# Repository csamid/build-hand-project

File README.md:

# CSULB BUILD Hand Project

As an CSULB NIH BUILD Scholar I worked in the Robotics and Interactive Systems Engineering laboratory on a hand rehabilitation project. This project was co-advised by Dr. Panadda Marayong and Dr. I-Hung Khoo (many thanks to them!). The goal of our project was to measure hand forces and torques for evaluation and rehabilitative training of individuals with hand impairment. Our project consists of a knob device and a grip-load device to simulate interactions that involve power and precision. Below you can find more details on each device and some other work I did.

> [!NOTE]
> This repo is primary for future csulb students that will build ontop of the work I and many previous students developed. However anyone can view/use the material. Feel free to contact me if you have any questions!

## Contents
- [Grip Load Device](#grip-load-device)
- [Brace](#bracee)
- [Knob Device](#knob-device)
- [Hapkit](#hapkit)

## GRIP LOAD DEVICE
The Grip-Load Device (GLD) runs on a Arduino Uno and incorporates data from three sensors:
- MPU6050 for acceleration to measure load force during dynamic tests. 
- LCFD-50 load cell to capture grip force 
- LSB302 Futek load cell to assess load force during static tests

The purpose of this device is to assess the differences in grip-load force coordination between healthy and hand impaired individuals. We also hope this device can provide rehabilitative training to individuals with hand impairment.

Dive deeper into the Grip Load Device:

# Brace
A 2 piece 3d printed adjustable brace to explore the effects of wrist position on grip-load force coordination. It can be set at -30, 0, and 30 degrees at the wrist.

Head to the Brace directory: 

<div style="text-align: center; padding-bottom: 50px;">

</div>

# Knob Device
The knob device centers around an Arduino Uno, sending data to a  graphical user interface (GUI) and controlling a haptic interface. This device aims to assess the coordination between grasping force and  turning torque. LabVIEW  handles the GUI and data acquisition. The haptic interface comprises a HEDS encoder, a maxon A-max motor, force sensing resistors  (FSR), and a torque sensor.

Dive deeper into the Knob Device:

# Hapkit
Some design changes were made to the open-source Hapkit 10.01.14 from Stanford to fit with available hardware at the RISE Lab @CSULB.

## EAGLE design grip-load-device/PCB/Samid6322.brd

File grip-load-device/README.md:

## Grip Load Device

Project Timeline (August 2021 - June 2022)

Check out my [presentation poster](assets/RSCA2022_Samid_Ceballos.pdf) to learn more!

#### For Students:
This repo contains the code, documentation, and parts for this device. The data collection is done on LabVIEW. Videos explaining how to download code, how arduino & LabVIEW code works, and how run the code can be found [here](https://www.youtube.com/playlist?list=PLc3eWZpUKAzyQBUwwpyzYRb3LxGoiJ5aO ).

### Bill of Materials
| Category    | Product                                       | Description                                    | Individual Quantity Needed |
| -----------  | -------------------------------------------- | ---------------------------------------------- | -------------------------- |
| Hardware    |                                              |                                                |                           |
|             | [Hex Socket Head Cap Screws](https://www.mcmaster.com/91251A346/)                    | 10-32, 7/8", Alloy Steel                      | 2                         |
|             | [Socket Head Screw](https://www.mcmaster.com/93615A380/)                             | 10-32, 1/2"                                  | 1                         |
|             | [Heat Threaded Inserts](https://www.mcmaster.com/93365A154/)                          | 10-32, 0.225"                                | 1                         |
| Electronics |                                              |                                                |                           |
|             | CSG110                                       | Strain gauge amplifier for the LSB302         | 1                         |
|             | LCFD-50                                      | Load Cell for Grip Force                      | 1                         |
|             | Futek LSB302                                 | Load Cell for Load Force                      | 1                         |
|             | MPU-6050                                    | 6-DOF Accl and Gyro sensor                    | 1                         |
|             | HX711                                       | Load Cell Amplifier                           | 1                         |
|             | Arduino Uno                                 | microcontroller                               | 1                         |
|             | PCB                                         | made in house by Dr. Khoo                    | 1                         |
| 3D Printed Parts |                                    |                                                |                           |
|                 | bottom_collar2                           | printed in CSULB's Innovation Space (Markforge Printer, onyx material)   | 1   |
|                 | plate_attachment                          | printed in CSULB's Innovation Space (Markforge Printer, onyx material)   | 2   |
|                 | top_collar2                              | printed in CSULB's Innovation Space (Markforge Printer, onyx material)   | 1   |
|                 | weightcomp                               | printed in CSULB's Innovation Space (Markforge Printer, onyx material)   | 1   |

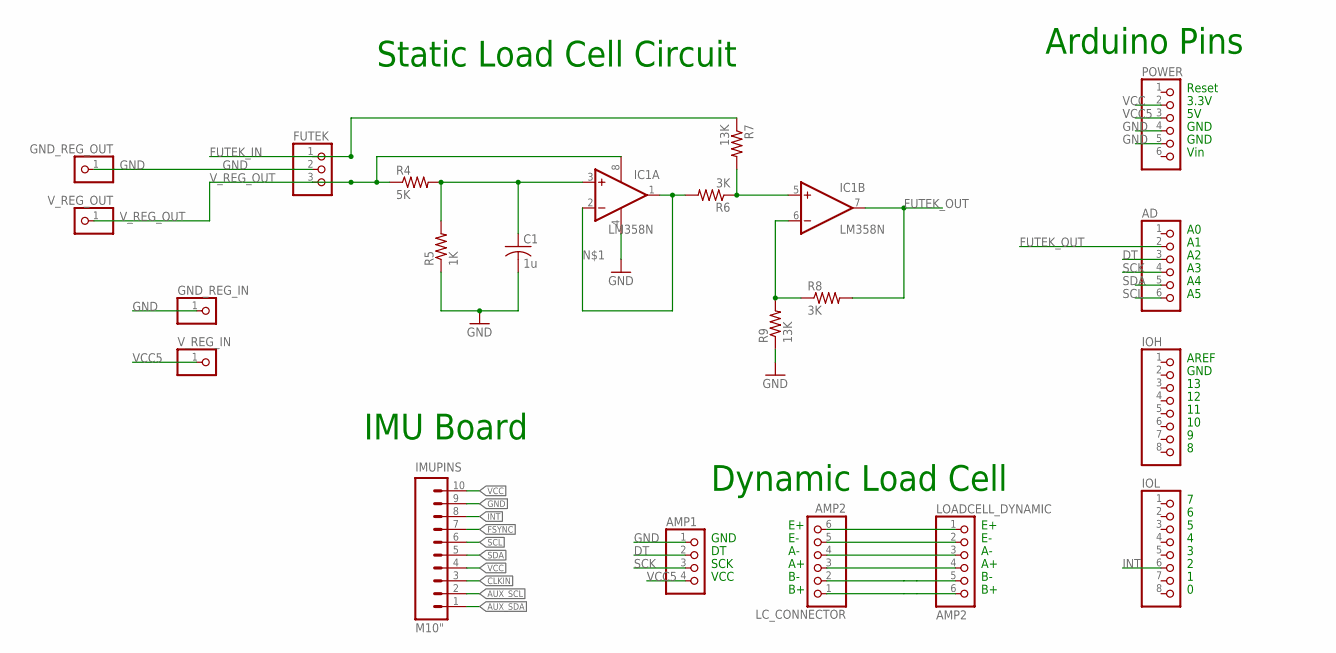
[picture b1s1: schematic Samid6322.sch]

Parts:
AD: PINHD-1X6; 1X06
AMP1: PINHD-1X4; 1X04
C1: 1u; C025-024X044
FUTEK: PINHD-1X3; 1X03
GND_REG_IN: PINHD-1X1; 1X01
GND_REG_OUT: PINHD-1X1; 1X01
IC1: LM358N; DIL08
IMUPINS: M10"; 1X10
IOH: PINHD-1X8; 1X08
IOL: PINHD-1X8; 1X08
LC_CONNECTOR: AMP2; 1X06
LOADCELL_DYNAMIC: AMP2; 1X06
POWER: PINHD-1X6; 1X06
R4: 5K; 0204/7
R5: 1K; 0204/7
R6, R8: 3K; 0204/7
R7, R9: 13K; 0204/7
V_REG_IN: PINHD-1X1; 1X01
V_REG_OUT: PINHD-1X1; 1X01

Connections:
AUX_SCL: IMUPINS.2
AUX_SDA: IMUPINS.1
CLKIN: IMUPINS.3
DT: AD.3, AMP1.2
FSYNC: IMUPINS.7
FUTEK_IN: FUTEK.1, R7.1
FUTEK_OUT: AD.2, IC1.7 (OUT), R8.2
GND: AMP1.1, C1.2, FUTEK.2, GND_REG_IN.1, GND_REG_OUT.1, IC1.4 (V-), IMUPINS.9, POWER.4, POWER.5, R5.1, R9.1
INT: IMUPINS.8, IOL.6
unnamed: IC1.1 (OUT), IC1.2 (-IN), R6.2
unnamed: LC_CONNECTOR.6, LOADCELL_DYNAMIC.1
unnamed: LC_CONNECTOR.5, LOADCELL_DYNAMIC.2
unnamed: LC_CONNECTOR.4, LOADCELL_DYNAMIC.3
unnamed: LC_CONNECTOR.3, LOADCELL_DYNAMIC.4
unnamed: LC_CONNECTOR.2, LOADCELL_DYNAMIC.5
unnamed: LC_CONNECTOR.1, LOADCELL_DYNAMIC.6
unnamed: IC1.5 (+IN), R6.1, R7.2
unnamed: C1.1, IC1.3 (+IN), R4.2, R5.2
unnamed: IC1.6 (-IN), R8.1, R9.2
SCK: AD.4, AMP1.3
SCL: AD.6, IMUPINS.6
SDA: AD.5, IMUPINS.5
VCC: IMUPINS.4, IMUPINS.10, POWER.2
VCC5: AMP1.4, POWER.3, V_REG_IN.1
V_REG_OUT: FUTEK.3, IC1.8 (V+), R4.1, V_REG_OUT.1

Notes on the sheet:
Reset
3.3V
GND
Vin
AREF
SCK
VCC
IMU Board
Dynamic Load Cell
Arduino Pins
Static Load Cell Circuit

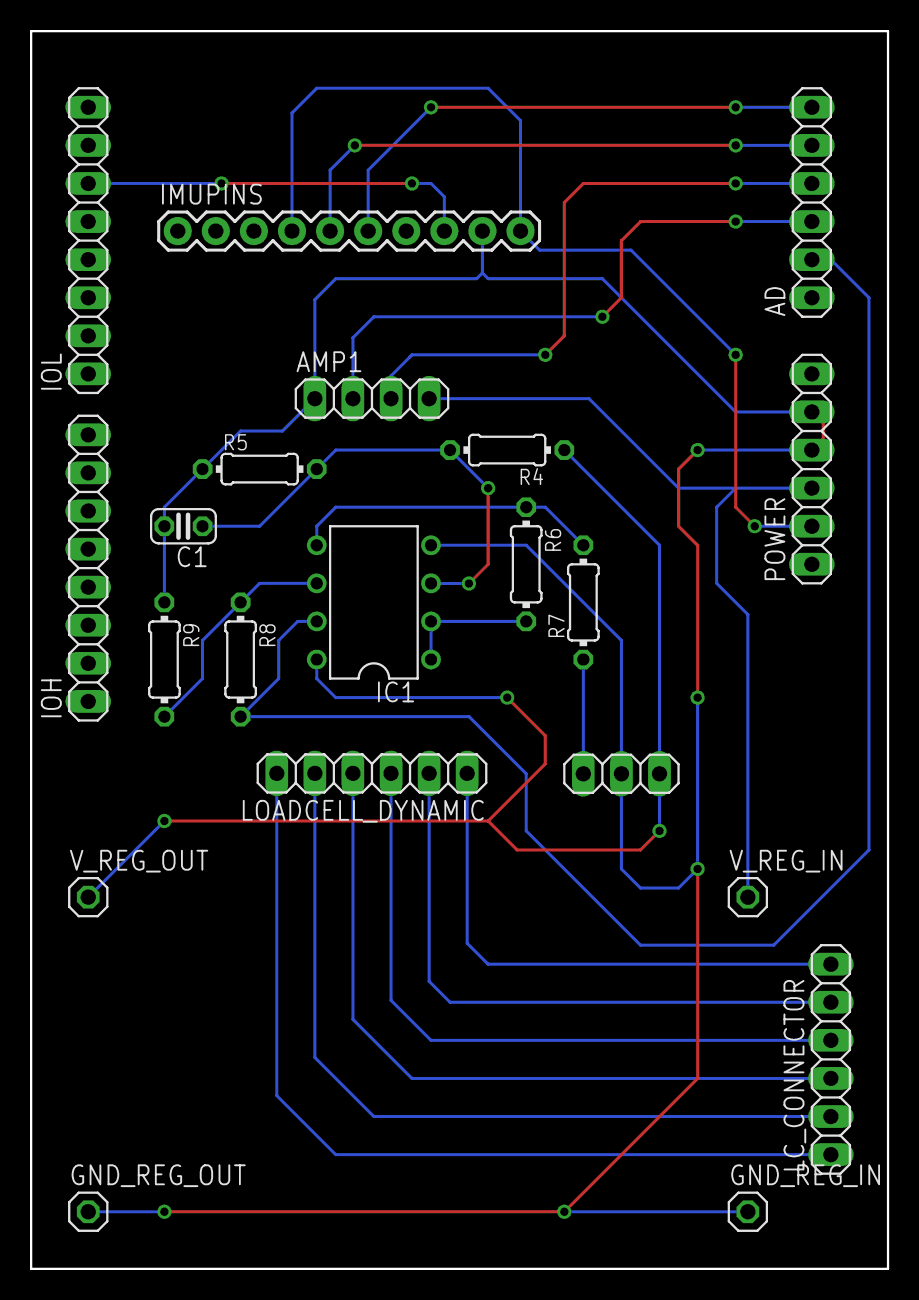
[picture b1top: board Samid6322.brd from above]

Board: 2 copper layers, 57.1 x 82.5 mm, 21 parts (0 on the bottom side), 21 nets.

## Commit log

2022-06-27 arduino code
2022-06-27 daniela's docs
2022-06-27 daniela's LV
2022-06-27 final solidworks files
2022-06-27 LabVIEW files
2022-06-27 pcb files, datasheets, and references
2022-06-27 old solidworks files
2022-06-27 BOM etc.
2022-06-27 Create brace
2022-06-27 sw files
2022-06-27 3d print files, and papers
2022-06-27 Create kd
2022-06-27 LV files
2022-06-27 papers and datasheets
2022-06-27 Create hk
2022-06-27 hapkit stuff
2022-06-27 pics for posters
2022-06-27 posters
2022-07-15 2019 LV
2022-07-26 2019 Ver LV for GLD
2022-09-24 Calibration for omega (GF) sensor
2022-09-24 logs and notes
2022-09-24 matlab cal files
2023-12-14 clean up
